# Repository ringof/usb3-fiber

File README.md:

# USB3-over-Fiber Link

USB3 SuperSpeed carried over an optical fiber link, using a **DS100BR111**
redriver into a **10GbE SR SFP+** optical module. A single symmetric PCB serves
both ends of the link — host-side and remote-side roles are selected by jumpers.
The **MCP2221A** provides the SFP+ management (I²C) interface and GPIO for
`TX_DISABLE` / `RX_LOS`. **No microcontroller, no firmware, no EEPROM.**

Built as the remote front-end for an SDR receiver: put the ADC at the antenna
and stream USB3 back to the shack over fiber.

## How it works

```
USB3-A connector        ┌───────────────┐        SFP+ cage
(SuperSpeed pairs) ─────►│  DS100BR111   │◄─────► (optical module) ──► fiber
                        │ (pin-strapped, │
                        │   3.3V)        │
                         └───────────────┘
                                │ SDA/SCL
                          ┌───────────┐
                          │ MCP2221A  │── USB micro-B ── laptop (SFP+ mgmt)
                          └───────────┘
```

Each fiber link needs **two identical boards** — one at the antenna, one at the
shack — with jumpers `JP1`/`JP2` selecting the role. The USB3 path is fully
symmetric: the DS100BR111 is bidirectional and the SFP+ module handles both TX
and RX in one cage.

## Central hypothesis

This prototype exists to test one thing:

> A 10GbE SR SFP+ optical module will transport USB3 SuperSpeed signalling
> intact — LFPS bursts, link training, electrical-idle transitions,
> spread-spectrum clocking, and receiver detection — without modifying the
> module or the USB3 endpoints.

It has been done in the amateur-radio and USB-extension communities, but it is
guaranteed by no specification. See
[`docs/USB3_Fiber_Link_Minimal_Circuit.md`](docs/USB3_Fiber_Link_Minimal_Circuit.md)
for the architecture, channel assignment, and the failure modes this board is
built to probe.

## Repository layout

| Path | Contents |
|---|---|
| `usb3_fiber.kicad_pro/.kicad_sch/.kicad_pcb` | The design. |
| `usb3_fiber.kicad_dru` | Custom high-speed design rules (length/skew/coupling/isolation/via-count). |
| `fp-lib-table` / `sym-lib-table` | Project-local library tables (`${KIPRJMOD}`). |
| `library/` | Symbols (`usb3_fiber.kicad_sym`), footprints (`.pretty/`), 3D models (`3dmodels/`). |
| `datasheets/` | Component datasheets. |
| `docs/` | Design intent, fab spec, turnkey/CI pipeline, release strategy, and the repo migration plan. |

## Requirements

- **KiCad 10.0** (latest stable 10.0.4) — the project baseline.

## Building the manufacturing outputs

From the repo root, with `kicad-cli` (KiCad 10):

```sh
kicad-cli sch erc   usb3_fiber.kicad_sch --output erc.rpt
kicad-cli pcb drc   usb3_fiber.kicad_pcb --output drc.rpt   # honors .kicad_dru
kicad-cli sch export pdf     usb3_fiber.kicad_sch --output schematic.pdf
kicad-cli sch export bom     usb3_fiber.kicad_sch --output bom.csv
kicad-cli pcb export gerbers usb3_fiber.kicad_pcb --output gerbers/
kicad-cli pcb export drill   usb3_fiber.kicad_pcb --output gerbers/
kicad-cli pcb export pos     usb3_fiber.kicad_pcb --output cpl.csv
kicad-cli pcb export step    usb3_fiber.kicad_pcb --output usb3_fiber.step
```

## Fabrication

4-layer FR4, ENIG, controlled impedance (100 Ω differential on the high-speed
pairs), targeting **JLCPCB's standard 4-layer process**. Full stackup,
impedance, and drill/feature constraints are in
[`docs/fab_specification.txt`](docs/fab_specification.txt).

## Downloads

Latest release (see [all releases](../../releases)):

- 📄 **[Schematic (PDF)](https://github.com/ringof/usb3-fiber/releases/latest/download/usb3_fiber-schematic.pdf)**
- 🧩 **[Assembly drawing (PDF)](https://github.com/ringof/usb3-fiber/releases/latest/download/usb3_fiber-assembly.pdf)** — top + bottom component placement
- 📐 **[Fabrication drawing (PDF)](https://github.com/ringof/usb3-fiber/releases/latest/download/usb3_fiber-fabrication-drawing.pdf)** — overview/spec, per-layer, and drill maps
- 🛠 **[Gerbers — JLCPCB-ready (zip)](https://github.com/ringof/usb3-fiber/releases/latest/download/usb3_fiber-gerbers.zip)**
- 📦 **[Full fabrication + design package (zip)](https://github.com/ringof/usb3-fiber/releases/latest/download/usb3_fiber-fabrication.zip)** — Gerbers, drill, BOM, CPL, schematic PDF, assembly + fabrication drawings, STEP

Packages are built and version-stamped by CI. Versioning is semantic
(`vMAJOR.MINOR`): `dev` publishes `v0.x` pre-releases, and promotion to `main`
cuts production releases (`v1.0`, then `v2.0`, …). The version and git hash are
stamped into the title block and bottom silkscreen at build time, and named in
each release's title/tag. The download links above resolve to the newest
**production** release; during the pre-1.0 phase (only `v0.x` pre-releases so
far), grab the assets from the specific pre-release on the
[Releases page](../../releases). See
[`docs/RELEASE_STRATEGY.md`](docs/RELEASE_STRATEGY.md) for how versions and
releases work (a new version is cut only when the design changes).

## Status

Prototype. This is an unproven design intended to validate the central
hypothesis above. The current revision is whatever the latest
[release](../../releases) is — it's stamped into the board, not hardcoded here.

## License

[CERN-OHL-P v2](LICENSE) (CERN Open Hardware Licence Version 2 – Permissive,
SPDX `CERN-OHL-P-2.0`).

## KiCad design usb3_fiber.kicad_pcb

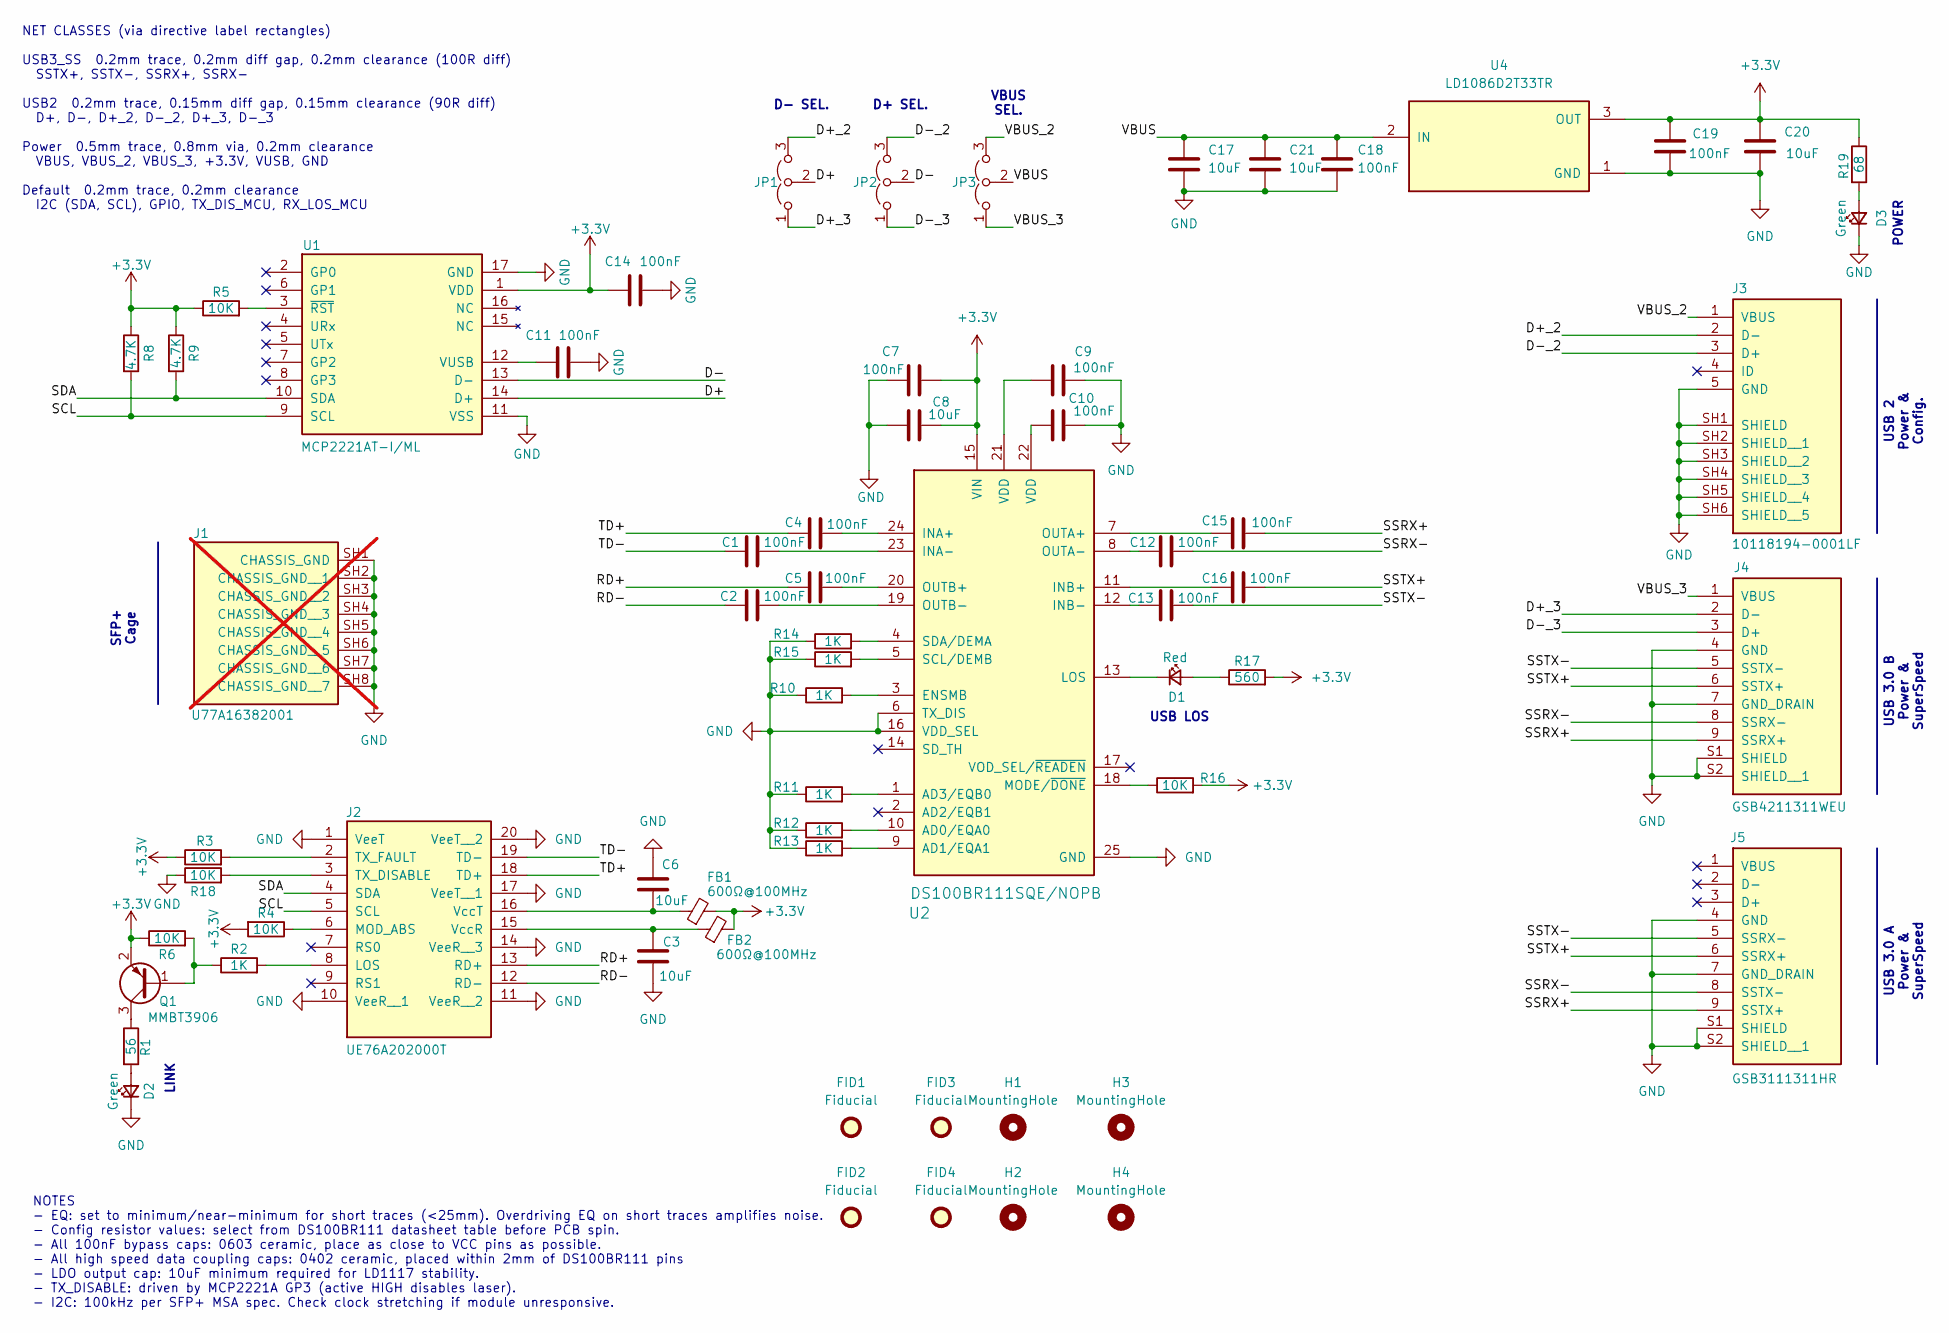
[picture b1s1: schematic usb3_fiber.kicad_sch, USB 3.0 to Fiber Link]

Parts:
C1, C2, C4, C5, C12, C13, C15, C16: 100nF; C_0402_1005Metric; Voltage 10V; Tolerance ±10%; Manufacturer Part Number CC0402KRX5R6BB104
C3, C6, C8, C17, C20, C21: 10uF; C_0805_2012Metric; Voltage 16V; Tolerance ±10%; Manufacturer Part Number CC0805KKX7R7BB106
C7, C9, C10, C14, C19: 100nF; C_0603_1608Metric; Voltage 10V; Tolerance ±10%; Manufacturer Part Number CC0603KRX7R6BB104
C11, C18: 100nF; C_0603_1608Metric; Voltage 16V; Tolerance ±10%; Manufacturer Part Number CC0603KRX7R7BB104
D1: Red; LED_0603_1608Metric; Manufacturer Part Number LTST-C190EKT
D2, D3: Green; LED_0603_1608Metric; Manufacturer Part Number LTST-C190GKT
FB1, FB2: 600Ω@100MHz; L_0603_1608Metric; Manufacturer Part Number BLM18KG601SN1D
FID1, FID2, FID3, FID4: Fiducial; Fiducial_1mm_Mask2mm
H1, H2, H3, H4: MountingHole; MountingHole_2.7mm_M2.5
J1: U77A16382001; AMPHENOL_U77A16382001; PARTREV B; not fitted
J2: UE76A202000T; AMPHENOL_UE76A202000T; PARTREV G
J3: 10118194-0001LF; AMPHENOL_10118194-0001LF; PARTREV D
J4: GSB4211311WEU; AMPHENOL_GSB4211311WEU; PARTREV B
J5: GSB3111311HR; AMPHENOL_GSB3111311HR
JP1, JP2, JP3: Jumper_3_Open; SolderJumper-3_P1.3mm_Open_Pad1.0x1.5mm
Q1: MMBT3906; SOT-23
R1: 56; R_0603_1608Metric; Tolerance ±1%; Manufacturer Part Number RC0603FR-0756RL
R2, R10, R11, R12, R13, R14, R15: 1K; R_0603_1608Metric; Tolerance ±1%; Manufacturer Part Number RC0603FR-071KL
R3, R4, R5, R6, R16, R18: 10K; R_0603_1608Metric; Tolerance ±1%; Manufacturer Part Number RC0603FR-0710KL
R8, R9: 4.7K; R_0603_1608Metric; Tolerance ±1%; Manufacturer Part Number RC0603FR-074K7L
R17: 560; R_0603_1608Metric; Tolerance ±1%; Manufacturer Part Number RC0603FR-07560RL
R19: 68; R_0603_1608Metric; Tolerance ±1%; Manufacturer Part Number RC0603FR-0768RL
U1: MCP2221AT-I/ML; QFN16_ML_MCH; Manufacturer Part Number MCP2221AT-I/ML
U2: DS100BR111SQE/NOPB; RTW24_2P6X2P6_TEX; Manufacturer Part Number DS100BR111SQE/NOPB
U4: LD1086D2T33TR; D2PAK_STM

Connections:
+3.3V: C7.2, C8.2, C14.1, C19.1, C20.1, FB1.2, FB2.2, Q1.2 (E), R3.1, R4.2, R5.1, R6.1, R8.1, R9.1, R16.2, R17.2, R19.1, U1.1 (VDD), U2.15 (VIN), U4.3 (OUT)
/D+: JP1.2 (C), U1.14 (D+)
/D+_2: J3.2 (D-), JP1.3 (B)
/D+_3: J4.2 (D-), JP1.1 (A)
/D-: JP2.2 (C), U1.13 (D-)
/D-_2: J3.3 (D+), JP2.3 (B)
/D-_3: J4.3 (D+), JP2.1 (A)
/RD+: C5.1, J2.13 (RD+)
/RD-: C2.1, J2.12 (RD-)
/SCL: J2.5 (SCL), R8.2, U1.9 (SCL)
/SDA: J2.4 (SDA), R9.2, U1.10 (SDA)
/SSRX+: C15.2, J4.9 (SSRX+), J5.9 (SSTX+)
/SSRX-: C12.2, J4.8 (SSRX-), J5.8 (SSTX-)
/SSTX+: C16.2, J4.6 (SSTX+), J5.6 (SSRX+)
/SSTX-: C13.2, J4.5 (SSTX-), J5.5 (SSRX-)
/TD+: C4.1, J2.18 (TD+)
/TD-: C1.1, J2.19 (TD-)
/VBUS: C17.1, C18.1, C21.1, JP3.2 (C), U4.2 (IN)
/VBUS_2: J3.1 (VBUS), JP3.3 (B)
/VBUS_3: J4.1 (VBUS), JP3.1 (A)
GND: C3.1, C6.1, C7.1, C8.1, C9.2, C10.2, C11.2, C14.2, C17.2, C18.2, C19.2, C20.2, C21.2, D2.1 (K), D3.1 (K), J1.SH1 (CHASSIS_GND), J1.SH2 (CHASSIS_GND__1), J1.SH3 (CHASSIS_GND__2), J1.SH4 (CHASSIS_GND__3), J1.SH5 (CHASSIS_GND__4), J1.SH6 (CHASSIS_GND__5), J1.SH7 (CHASSIS_GND__6), J1.SH8 (CHASSIS_GND__7), J2.1 (VeeT), J2.10 (VeeR__1), J2.11 (VeeR__2), J2.14 (VeeR__3), J2.17 (VeeT__1), J2.20 (VeeT__2), J3.5 (GND), J3.SH1 (SHIELD), J3.SH2 (SHIELD__1), J3.SH3 (SHIELD__2), J3.SH4 (SHIELD__3), J3.SH5 (SHIELD__4), J3.SH6 (SHIELD__5), J4.4 (GND), J4.7 (GND_DRAIN), J4.S1 (SHIELD), J4.S2 (SHIELD__1), J5.4 (GND), J5.7 (GND_DRAIN), J5.S1 (SHIELD), J5.S2 (SHIELD__1), R10.1, R11.1, R12.1, R13.1, R14.1, R15.1, R18.1, U1.11 (VSS), U1.17 (GND), U2.6 (TX_DIS), U2.16 (VDD_SEL), U2.25 (GND), U4.1 (GND)
unnamed: C9.1, U2.21 (VDD)
unnamed: C10.1, U2.22 (VDD)
unnamed: D1.2 (A), R17.1
unnamed: D1.1 (K), U2.13 (LOS)
unnamed: D2.2 (A), R1.2
unnamed: D3.2 (A), R19.2
unnamed: J2.8 (LOS), R2.2
unnamed: J2.6 (MOD_ABS), R4.1
unnamed: J2.3 (TX_DISABLE), R18.2
unnamed: J2.2 (TX_FAULT), R3.2
unnamed: C3.2, FB2.1, J2.15 (VccR)
unnamed: C6.2, FB1.1, J2.16 (VccT)
unnamed: Q1.1 (B), R2.1, R6.2
unnamed: Q1.3 (C), R1.1
unnamed: C11.1, U1.12 (VUSB)
unnamed: R5.2, U1.3 (~RST)
unnamed: R12.2, U2.10 (AD0/EQA0)
unnamed: R13.2, U2.9 (AD1/EQA1)
unnamed: R11.2, U2.1 (AD3/EQB0)
unnamed: R10.2, U2.3 (ENSMB)
unnamed: C4.2, U2.24 (INA+)
unnamed: C1.2, U2.23 (INA-)
unnamed: C16.1, U2.11 (INB+)
unnamed: C13.1, U2.12 (INB-)
unnamed: R16.1, U2.18 (MODE/~DONE)
unnamed: C15.1, U2.7 (OUTA+)
unnamed: C12.1, U2.8 (OUTA-)
unnamed: C5.2, U2.20 (OUTB+)
unnamed: C2.2, U2.19 (OUTB-)
unnamed: R15.2, U2.5 (SCL/DEMB)
unnamed: R14.2, U2.4 (SDA/DEMA)

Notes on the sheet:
NOTES - EQ: set to minimum/near-minimum for short traces (<25mm). Overdriving EQ on short traces amplifies noise. - Config resistor values: select from DS100BR111 datasheet table before PCB spin. - All 100nF bypass caps: 0603 ceramic, place as close to VCC pins as possible. - All high speed data co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
NET CLASSES (via directive label rectangles) USB3_SS 0.2mm trace, 0.2mm diff gap, 0.2mm clearance (100R diff) SSTX+, SSTX-, SSRX+, SSRX- USB2 0.2mm trace, 0.15mm diff gap, 0.15mm clearance (90R diff) D+, D-, D+_2, D-_2, D+_3, D-_3 Power 0.5mm trace, 0.8mm via, 0.2mm clearance VBUS, VBUS_2, VBUS_3, 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
USB 2 Power & Config.
SFP+ Cage
D- SEL.
POWER
VBUS SEL.
USB 3.0 A Power & SuperSpeed
USB LOS
D+ SEL.
USB 3.0 B Power & SuperSpeed
LINK

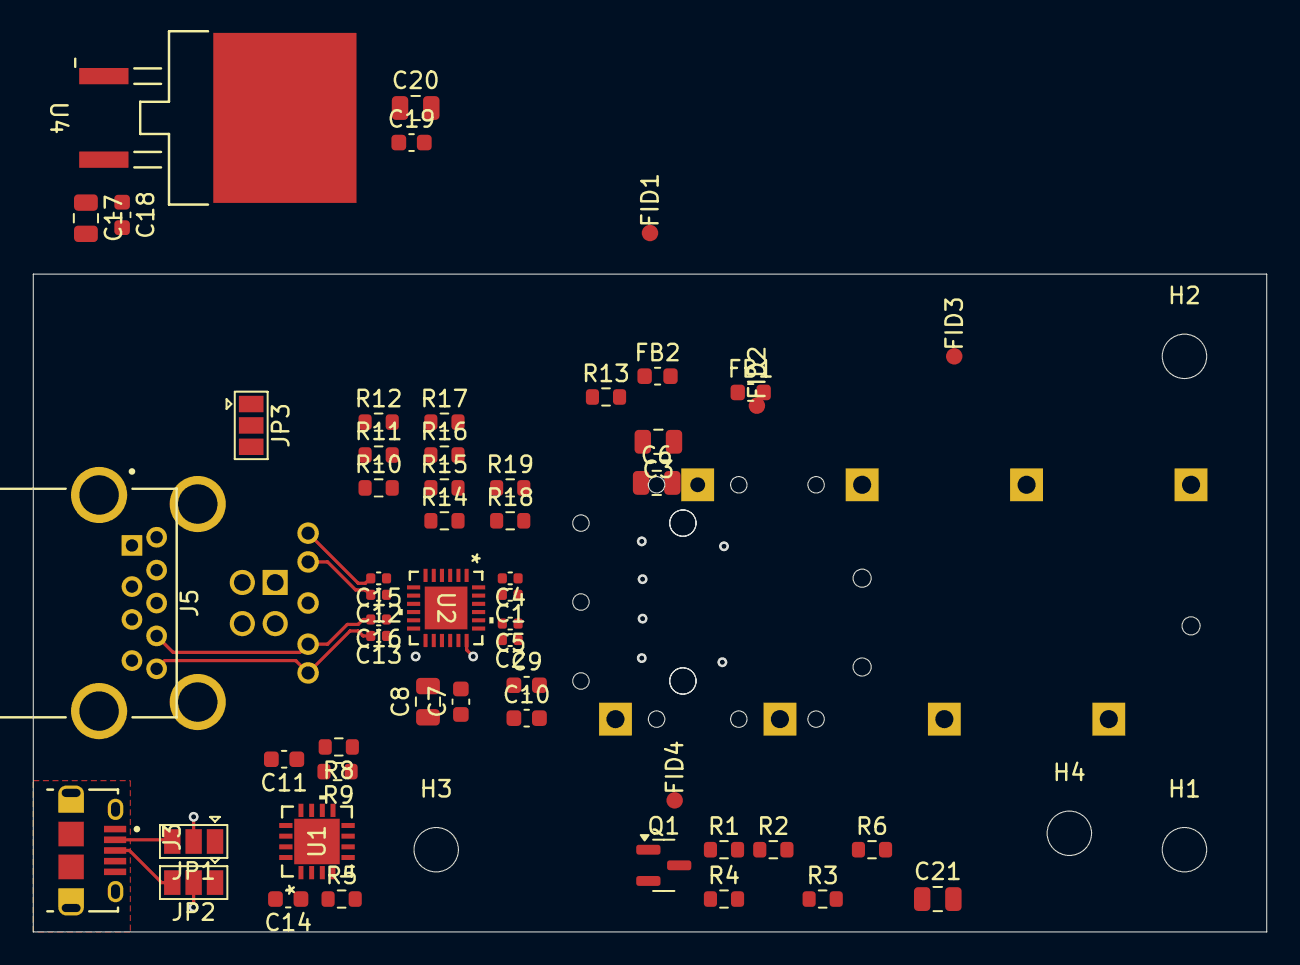
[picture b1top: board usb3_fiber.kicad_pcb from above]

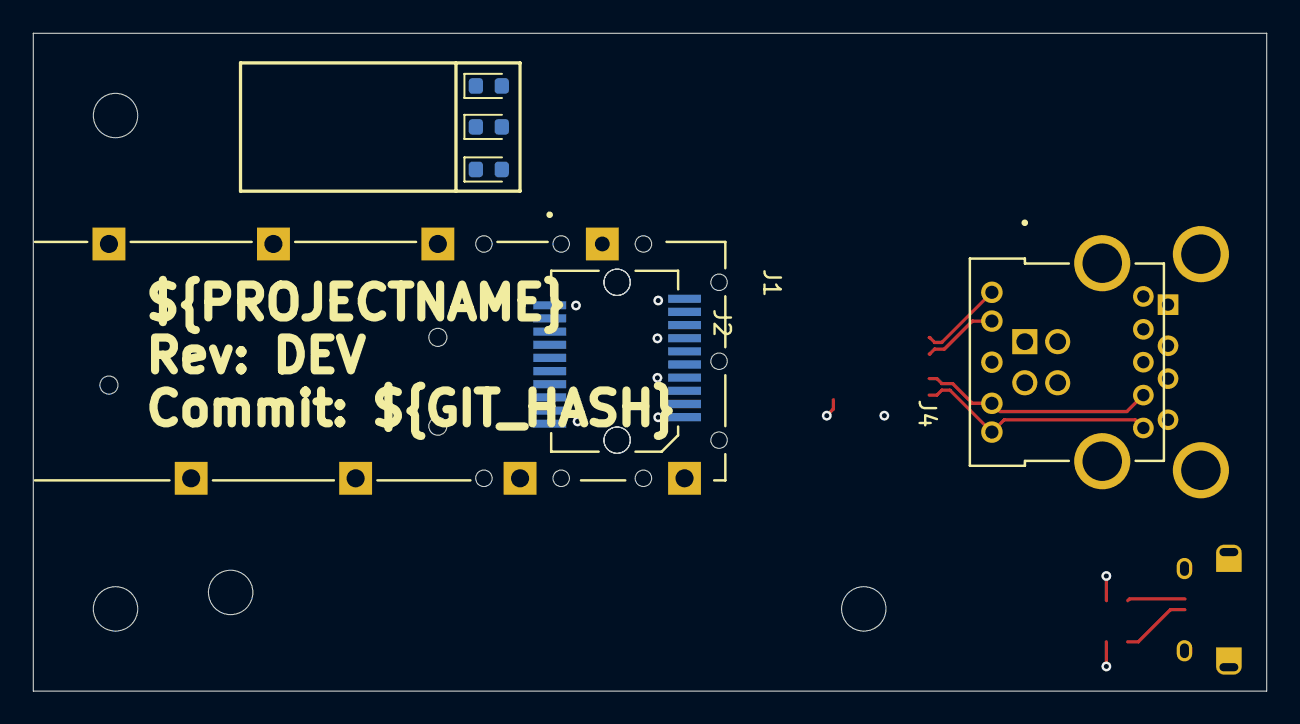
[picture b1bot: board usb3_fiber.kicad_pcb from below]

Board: 4 copper layers, 75.0 x 40.0 mm, 64 parts (6 on the bottom side), 52 nets.

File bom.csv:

"Reference","Value","Footprint","MPN","LCSC"
"C1","100nF","Capacitor_SMD:C_0402_1005Metric","CC0402KRX5R6BB104",""
"C2","100nF","Capacitor_SMD:C_0402_1005Metric","CC0402KRX5R6BB104",""
"C3","10uF","Capacitor_SMD:C_0805_2012Metric","CC0805KKX7R7BB106",""
"C4","100nF","Capacitor_SMD:C_0402_1005Metric","CC0402KRX5R6BB104",""
"C5","100nF","Capacitor_SMD:C_0402_1005Metric","CC0402KRX5R6BB104",""
"C6","10uF","Capacitor_SMD:C_0805_2012Metric","CC0805KKX7R7BB106",""
"C7","100nF","Capacitor_SMD:C_0603_1608Metric","CC0603KRX7R6BB104",""
"C8","10uF","Capacitor_SMD:C_0805_2012Metric","CC0805KKX7R7BB106",""
"C9","100nF","Capacitor_SMD:C_0603_1608Metric","CC0603KRX7R6BB104",""
"C10","100nF","Capacitor_SMD:C_0603_1608Metric","CC0603KRX7R6BB104",""
"C11","100nF","Capacitor_SMD:C_0603_1608Metric","CC0603KRX7R7BB104",""
"C12","100nF","Capacitor_SMD:C_0402_1005Metric","CC0402KRX5R6BB104",""
"C13","100nF","Capacitor_SMD:C_0402_1005Metric","CC0402KRX5R6BB104",""
"C14","100nF","Capacitor_SMD:C_0603_1608Metric","CC0603KRX7R6BB104",""
"C15","100nF","Capacitor_SMD:C_0402_1005Metric","CC0402KRX5R6BB104",""
"C16","100nF","Capacitor_SMD:C_0402_1005Metric","CC0402KRX5R6BB104",""
"C17","10uF","Capacitor_SMD:C_0805_2012Metric","CC0805KKX7R7BB106",""
"C18","100nF","Capacitor_SMD:C_0603_1608Metric","CC0603KRX7R7BB104",""
"C19","100nF","Capacitor_SMD:C_0603_1608Metric","CC0603KRX7R6BB104",""
"C20","10uF","Capacitor_SMD:C_0805_2012Metric","CC0805KKX7R7BB106",""
"C21","10uF","Capacitor_SMD:C_0805_2012Metric","CC0805KKX7R7BB106",""
"D1","Red","LED_SMD:LED_0603_1608Metric","LTST-C190EKT",""
"D2","Green","LED_SMD:LED_0603_1608Metric","LTST-C190GKT",""
"D3","Green","LED_SMD:LED_0603_1608Metric","LTST-C190GKT",""
"FB1","600Ω@100MHz","Inductor_SMD:L_0603_1608Metric","BLM18KG601SN1D",""
"FB2","600Ω@100MHz","Inductor_SMD:L_0603_1608Metric","BLM18KG601SN1D",""
"J2","UE76A202000T","usb3_fiber:AMPHENOL_UE76A202000T","UE76A202000T",""
"J3","10118194-0001LF","usb3_fiber:AMPHENOL_10118194-0001LF","10118194-0001LF",""
"J4","GSB4211311WEU","usb3_fiber:AMPHENOL_GSB4211311WEU","GSB4211311WEU",""
"J5","GSB3111311HR","usb3_fiber:AMPHENOL_GSB3111311HR","",""
"Q1","MMBT3906","Package_TO_SOT_SMD:SOT-23","",""
"R1","56","Resistor_SMD:R_0603_1608Metric","RC0603FR-0756RL",""
"R2","1K","Resistor_SMD:R_0603_1608Metric","RC0603FR-071KL",""
"R3","10K","Resistor_SMD:R_0603_1608Metric","RC0603FR-0710KL",""
"R4","10K","Resistor_SMD:R_0603_1608Metric","RC0603FR-0710KL",""
"R5","10K","Resistor_SMD:R_0603_1608Metric","RC0603FR-0710KL",""
"R6","10K","Resistor_SMD:R_0603_1608Metric","RC0603FR-0710KL",""
"R8","4.7K","Resistor_SMD:R_0603_1608Metric","RC0603FR-074K7L",""
"R9","4.7K","Resistor_SMD:R_0603_1608Metric","RC0603FR-074K7L",""
"R10","1K","Resistor_SMD:R_0603_1608Metric","RC0603FR-071KL",""
"R11","1K","Resistor_SMD:R_0603_1608Metric","RC0603FR-071KL",""
"R12","1K","Resistor_SMD:R_0603_1608Metric","RC0603FR-071KL",""
"R13","1K","Resistor_SMD:R_0603_1608Metric","RC0603FR-071KL",""
"R14","1K","Resistor_SMD:R_0603_1608Metric","RC0603FR-071KL",""
"R15","1K","Resistor_SMD:R_0603_1608Metric","RC0603FR-071KL",""
"R16","10K","Resistor_SMD:R_0603_1608Metric","RC0603FR-0710KL",""
"R17","560","Resistor_SMD:R_0603_1608Metric","RC0603FR-07560RL",""
"R18","10K","Resistor_SMD:R_0603_1608Metric","RC0603FR-0710KL",""
"R19","68","Resistor_SMD:R_0603_1608Metric","RC0603FR-0768RL",""
"U1","MCP2221AT-I/ML","usb3_fiber:QFN16_ML_MCH","MCP2221AT-I/ML",""
"U2","DS100BR111SQE/NOPB","usb3_fiber:RTW24_2P6X2P6_TEX","DS100BR111SQE/NOPB",""
"U4","LD1086D2T33TR","usb3_fiber:D2PAK_STM","",""
